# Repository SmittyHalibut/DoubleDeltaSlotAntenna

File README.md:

# Smitty's research into John Portune's Double Delta Skeleton Slot Antenna
This is my directory of stuff.  Let's see, I've got an OpenSCAD model for the top bracket,
I've got some drawings of the switching network I made, I've got the raw NanoVNA data
I collected...  I might have other stuff too, look at README.md files inside the directories.

* Notes and files for my [BayCon 2021](BayCon2021/) presentation
* Raw data, and analysis of data, from [NanoVNA Saver](NanoVNA%20Saver%20Files/) of my build of this antenna.
* Diagram for full [switching network](Switching/)
* OpenSCAD and `.stl` files for my top-of-mast [spreader bracket](Brackets/)

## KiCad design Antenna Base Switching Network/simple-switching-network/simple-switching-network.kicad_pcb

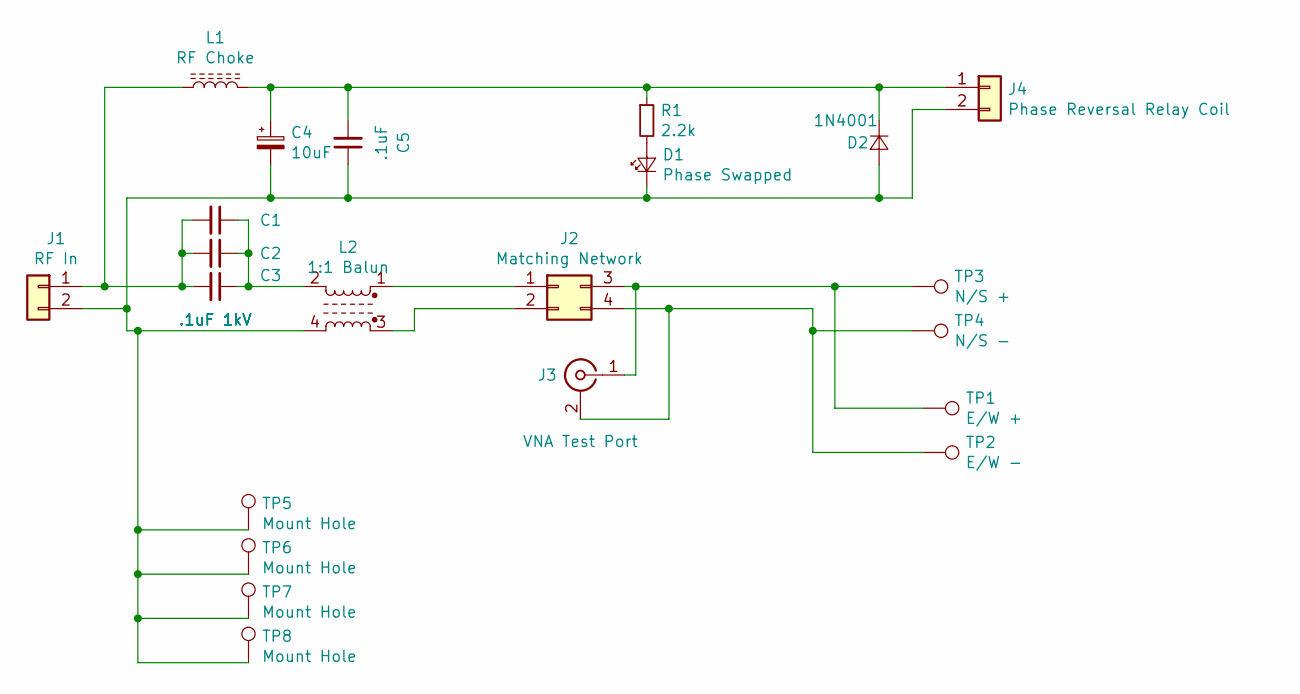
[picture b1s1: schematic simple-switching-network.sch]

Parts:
C1, C2, C3: .1uF 1kV; C_Rect_L10.0mm_W5.0mm_P5.00mm_P7.50mm
C4: 10uF; CP_Radial_D10.0mm_P2.50mm_P5.00mm
C5: .1uF; C_Rect_L7.0mm_W3.5mm_P2.50mm_P5.00mm
D1: Phase Swapped; LED_D5.0mm
D2: 1N4001; D_DO-41_SOD81_P10.16mm_Horizontal
J1: RF In; SolderWirePad_1x02_P5.08mm_Drill1.5mm
J2: Matching Network; MatchingNetworkModule
J3: VNA Test Port; SMA_Amphenol_132134-14_Vertical
J4: Phase Reversal Relay Coil; SolderWirePad_1x02_P5.08mm_Drill1.5mm
L1: RF Choke; L_Toroid_Vertical_L35.6mm_W17.8mm_P12.70mm_Pulse_E
L2: 1:1 Balun; Balun-FT140
R1: 2.2k; R_Axial_DIN0207_L6.3mm_D2.5mm_P10.16mm_Horizontal
TP1: E/W +; MountingHole_3.2mm_M3_Pad
TP2: E/W -; MountingHole_3.2mm_M3_Pad
TP3: N/S +; MountingHole_3.2mm_M3_Pad
TP4: N/S -; MountingHole_3.2mm_M3_Pad
TP5, TP6, TP7, TP8: Mount Hole; MountingHole_3.2mm_M3_Pad

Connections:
unnamed: C1.1, C2.1, C3.1, L2.2
unnamed: C1.2, C2.2, C3.2, J1.1, L1.1
unnamed: C4.1, C5.2, D2.1 (K), J4.1, L1.2, R1.1
unnamed: C4.2, C5.1, D1.1 (K), D2.2 (A), J1.2, J4.2, L2.4, TP5.1, TP6.1, TP7.1, TP8.1
unnamed: D1.2 (A), R1.2
unnamed: J2.1, L2.1
unnamed: J2.2, L2.3
unnamed: J2.3, J3.1 (In), TP1.1, TP3.1
unnamed: J2.4, J3.2 (Ext), TP2.1, TP4.1

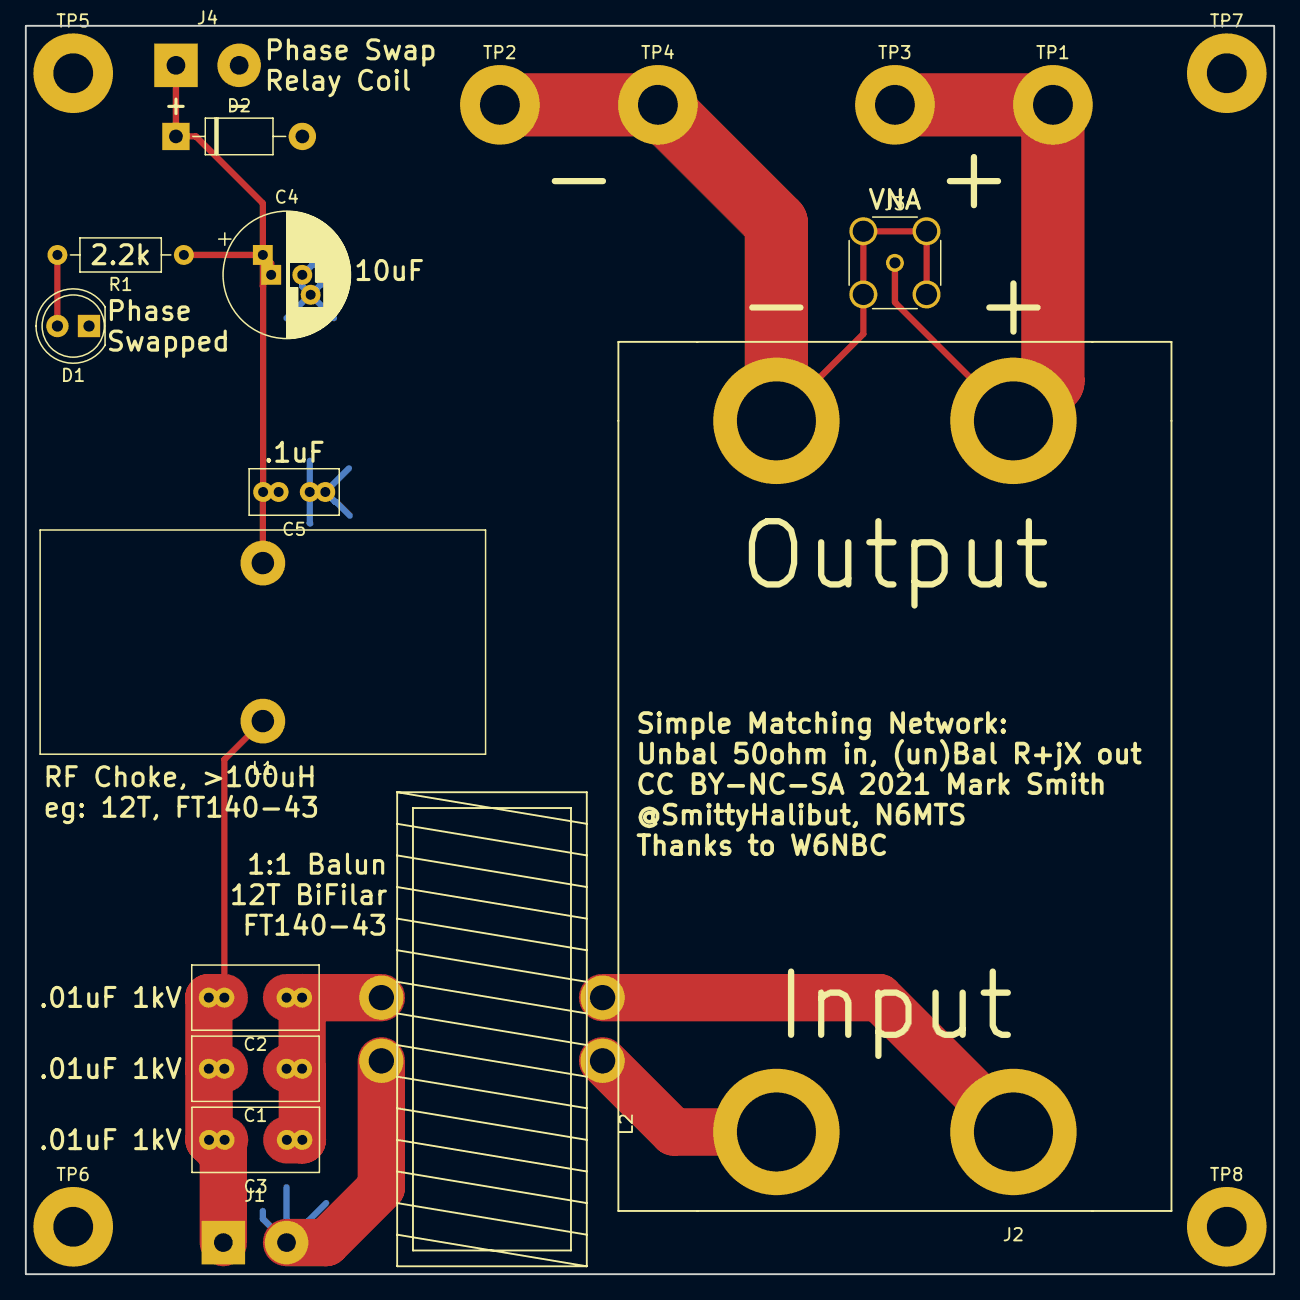
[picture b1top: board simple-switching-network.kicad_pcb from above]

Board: 2 copper layers, 100.3 x 100.3 mm, 22 parts (0 on the bottom side), 9 nets.

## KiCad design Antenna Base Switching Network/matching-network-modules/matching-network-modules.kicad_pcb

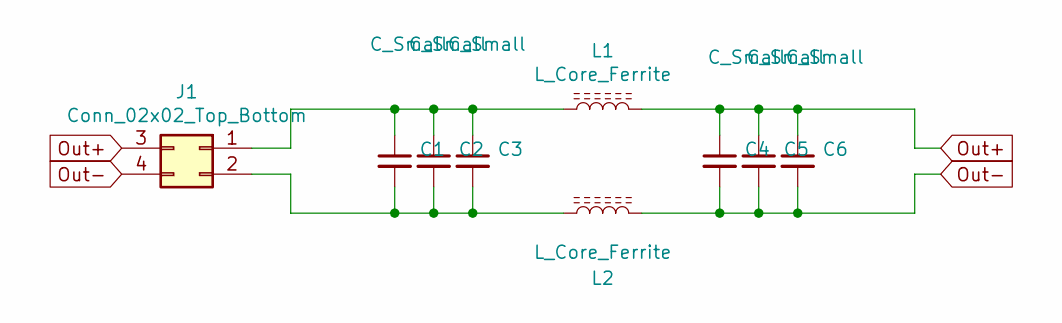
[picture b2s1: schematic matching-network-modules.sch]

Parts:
C1, C4: C_Small; C_Rect_L7.0mm_W3.5mm_P5.00mm
C2, C5: C_Small; C_Rect_L10.0mm_W4.0mm_P7.50mm_FKS3_FKP3
C3, C6: C_Small; C_Rect_L13.0mm_W5.0mm_P10.00mm_FKS3_FKP3_MKS4
J1: Conn_02x02_Top_Bottom; MatchingNetworkModule
L1, L2: L_Core_Ferrite; L_Toroid_Vertical_L41.9mm_W19.1mm_P15.80mm_Vishay_TJ7

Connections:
unnamed: C1.1, C2.1, C3.1, J1.1, L1.1
unnamed: C1.2, C2.2, C3.2, J1.2, L2.1
Out+: C4.1, C5.1, C6.1, J1.3, L1.2
Out-: C4.2, C5.2, C6.2, J1.4, L2.2

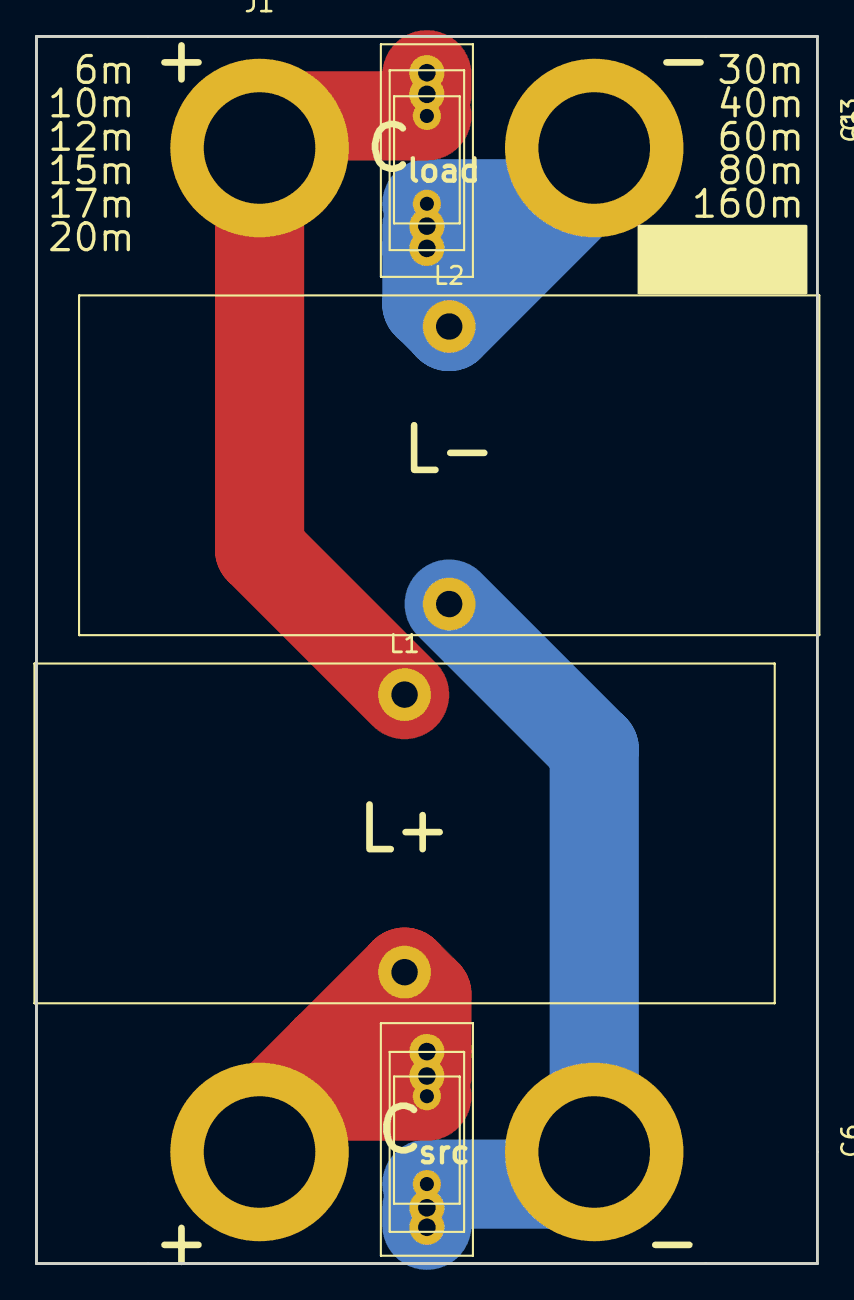
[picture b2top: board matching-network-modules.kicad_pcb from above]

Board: 2 copper layers, 44.4 x 69.8 mm, 9 parts (0 on the bottom side), 4 nets.

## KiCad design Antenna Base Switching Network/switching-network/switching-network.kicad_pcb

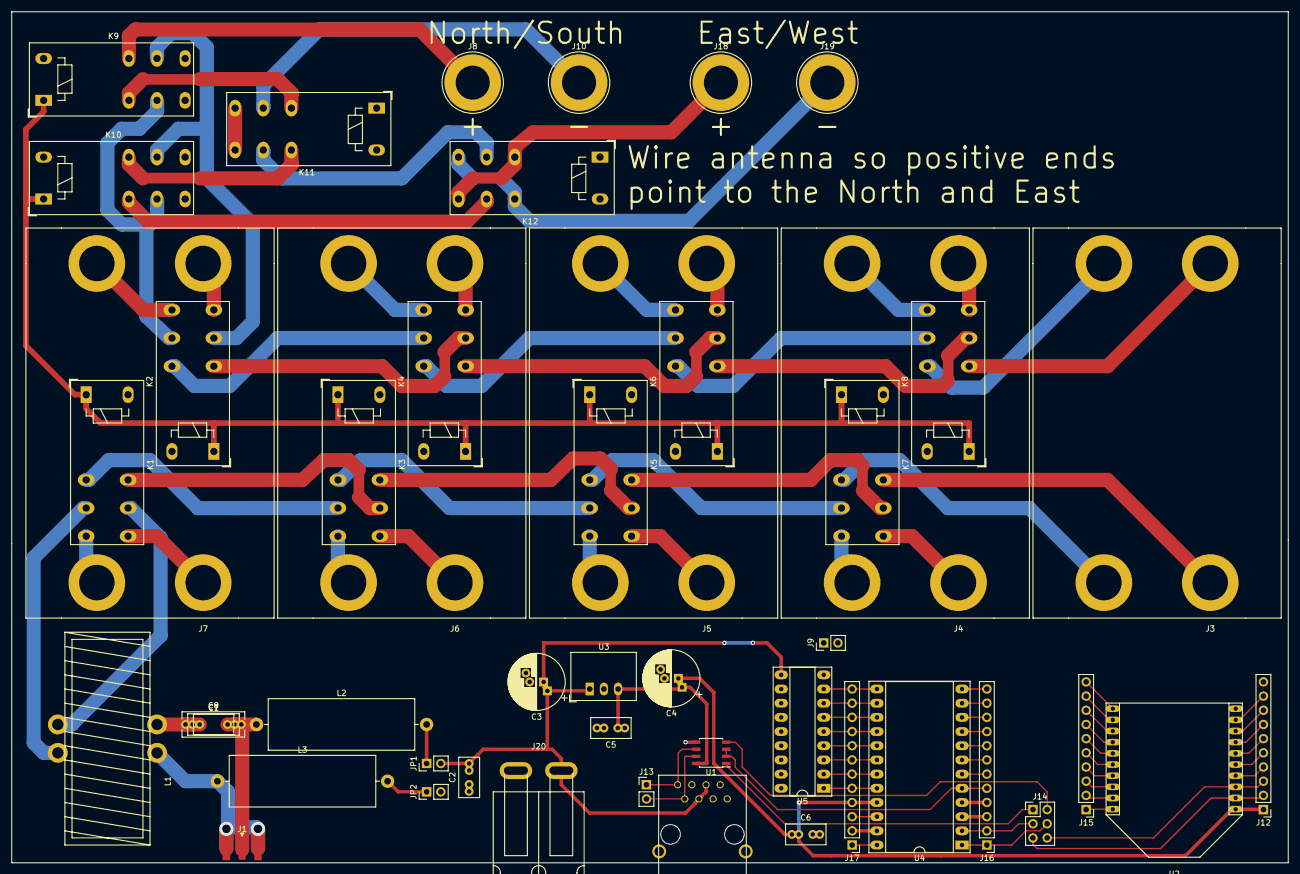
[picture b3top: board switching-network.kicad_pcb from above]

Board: 2 copper layers, 228.6 x 152.4 mm, 49 parts (0 on the bottom side), 103 nets.

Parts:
C1: .1uF; C_Rect_L7.0mm_W3.5mm_P5.00mm
C2, C5, C6: .1uF; C_Rect_L7.0mm_W3.5mm_P2.50mm_P5.00mm
C3, C4: 100uF; CP_Radial_D10.0mm_P2.50mm_P5.00mm
C7: .1uF; C_Rect_L9.0mm_W3.6mm_P7.50mm_MKT
C8: .1uF; C_Rect_L11.0mm_W4.3mm_P10.00mm_MKT
J1: Conn_Coaxial; SMA_Samtec_SMA-J-P-H-ST-EM1_EdgeMount
J3: Module 1 Socket; MatchingNetworkModule
J4: Module 2 Socket; MatchingNetworkModule
J5: Module 3 Socket; MatchingNetworkModule
J6: Module 4 Socket; MatchingNetworkModule
J7: Module 5 Socket; MatchingNetworkModule
J8: NS+; Banana_Jack_1Pin
J9: Simple Bias Tee Rotation Control; PinHeader_1x02_P2.54mm_Vertical
J10: NS-; Banana_Jack_1Pin
J11: 8P8C_Shielded; RJ-45
J12, J15: Test Points; PinHeader_1x10_P2.54mm_Vertical
J13: Test Points; PinHeader_1x02_P2.54mm_Vertical
J14: RS-485 vs XBee; PinHeader_2x03_P2.54mm_Vertical
J16, J17: Test Points; PinHeader_1x12_P2.54mm_Vertical
J18: EW+; Banana_Jack_1Pin
J19: EW-; Banana_Jack_1Pin
J20: +12v Power; AndersonPP45
JP1, JP2: Jumper_NC_Small; PinHeader_1x02_P2.54mm_Vertical
K1, K2, K3, K4, K5, K6, K7, K8: RT42xxxx; Relay_DPDT_Schrack-RT2-FormC_RM5mm
K9: N/S Disable; Relay_DPDT_Schrack-RT2-FormC_RM5mm
K10: E/W Disable; Relay_DPDT_Schrack-RT2-FormC_RM5mm
K11: Series Enable; Relay_DPDT_Schrack-RT2-FormC_RM5mm
K12: E/W Reverse; Relay_DPDT_Schrack-RT2-FormC_RM5mm
L1: 1:1 Balun; Balun-FT140
L2, L3: RF Choke; L_Axial_L26.0mm_D9.0mm_P30.48mm_Horizontal_Fastron_77A
U1: SN65HVD10-EP; SOIC-8_3.9x4.9mm_P1.27mm
U2: XBeeModule
U3: R-783.3-0.5; Converter_DCDC_RECOM_R-78E-0.5_THT
U4: Leonardo_Pro_Micro; DIP-24_W15.24mm_Socket_LongPads
U5: ULN2803A; DIP-18_W7.62mm_Socket_LongPads

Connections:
+3V3: C4.1, C5.1, C6.1, J12.1, J17.4, U1.8, U2.1, U3.3, U4.21
+12V: C2.2, C3.1, J11.4, J11.5, J20.1, JP1.2, K1.A1, K2.A1, K3.A1, K4.A1, K5.A1, K6.A1, K7.A1, K8.A1, K9.A1, K10.A1, K11.A1, K12.A1, U3.1, U5.10
EWDisable: K10.A2, U5.12
EWReverse: J9.1, K12.A2, U5.16
GND: C2.1, C3.2, C4.2, C5.2, C6.2, J9.2, J11.7, J11.8, J12.10, J16.3, J16.4, J17.2, J20.2, JP2.2, U1.5, U2.10, U3.2, U4.3, U4.4, U4.23, U5.9
MatchedRFOut+: K2.11, K9.21, K10.21
MatchedRFOut-: K2.21, K9.11, K10.11
Mod2En: K7.A2, K8.A2, U5.18
Mod3En: K5.A2, K6.A2, U5.17
Mod4En: K3.A2, K4.A2, U5.14
Mod5En: K1.A2, K2.A2, U5.13
ModIn1+: J3.1, K7.22
ModIn1-: J3.2, K7.12
ModIn2+: J4.1, K7.24
ModIn2-: J4.2, K7.14
ModIn3+: J5.1, K5.24
ModIn3-: J5.2, K5.14
ModIn4+: J6.1, K3.24
ModIn4-: J6.2, K3.14
ModIn5+: J7.1, K1.24
ModIn5-: J7.2, K1.14
ModOut1+: J3.3, K8.12
ModOut1-: J3.4, K8.22
ModOut2+: J4.3, K8.14
ModOut2-: J4.4, K8.24
ModOut3+: J5.3, K6.14
ModOut3-: J5.4, K6.24
ModOut4+: J6.3, K4.14
ModOut4-: J6.4, K4.24
ModOut5+: J7.3, K2.14
ModOut5-: J7.4, K2.24
NSDisable: K9.A2, U5.11
unnamed: C1.1, C7.1, C8.1, L1.1
unnamed: C1.2, C7.2, C8.2, J1.1, L2.1
unnamed: J1.2, L1.3, L3.1
unnamed: J8.1, K9.22
unnamed: J10.1, K11.11
unnamed: J11.1, J13.1, U1.6
unnamed: J11.2, J13.2, U1.7
unnamed: J12.4, U2.4
unnamed: J12.5, U2.5
unnamed: J12.6, U2.6
unnamed: J12.7, U2.7
unnamed: J12.8, U2.8
unnamed: J12.9, U2.9
unnamed: J15.1, U2.20
unnamed: J15.2, U2.19
unnamed: J15.3, U2.18
unnamed: J15.4, U2.17
unnamed: J15.5, U2.16
unnamed: J15.6, U2.15
unnamed: J15.7, U2.14
unnamed: J15.8, U2.13
unnamed: J15.9, U2.12
unnamed: J15.10, U2.11
unnamed: J16.6, U4.6
unnamed: J16.7, U4.7
unnamed: J16.8, U4.8
unnamed: J16.9, U4.9
unnamed: J16.10, U4.10
unnamed: J16.11, U4.11
unnamed: J16.12, U4.12
unnamed: J17.1, U4.24
unnamed: J17.5, U4.20, U5.1
unnamed: J17.6, U4.19, U5.2
unnamed: J17.7, U4.18, U5.3
unnamed: J17.8, U4.17, U5.4
unnamed: J17.9, U4.16, U5.5
unnamed: J17.10, U4.15, U5.6
unnamed: J17.11, U4.14, U5.7
unnamed: J17.12, U4.13, U5.8
unnamed: J18.1, K12.12, K12.24
unnamed: J19.1, K12.14, K12.22
unnamed: JP1.1, L2.2
unnamed: JP2.1, L3.2
unnamed: K1.11, L1.4
unnamed: K1.12, K3.11
unnamed: K1.21, L1.2
unnamed: K1.22, K3.21
unnamed: K2.12, K4.11
unnamed: K2.22, K4.21
unnamed: K3.12, K5.11
unnamed: K3.22, K5.21
unnamed: K4.12, K6.11
unnamed: K4.22, K6.21
unnamed: K5.12, K7.11
unnamed: K5.22, K7.21
unnamed: K6.12, K8.11
unnamed: K6.22, K8.21
unnamed: K10.12, K12.21
unnamed: K10.22, K11.22
unnamed: K9.12, K11.12
unnamed: K11.14, K11.24
unnamed: K11.21, K12.11
Reset: J17.3, U4.22
Rx485: J14.2, U1.4
RxMicro: J14.3, J16.2, U4.2
RxXBee: J12.3, J14.6, U2.3
SeriesEnable: K11.A2, U5.15
Tx485: J14.1, U1.1
TxEn485: J16.5, U1.2, U1.3, U4.5
TxMicro: J14.4, J16.1, U4.1
TxXBee: J12.2, J14.5, U2.2

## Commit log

2020-10-18 Initial commit: OpenSCAD bracket for mast topper, NanoVNA raw data files, and drawings of the switching network I made for researching.
2020-10-18 Images of the NanoVNA-Saver screen showing the stats for 40m, 30m, 20m, 15m, and 10m
2020-10-18 Adding detail to the README
2020-10-18 Adding link to nanovna-saver
2020-12-29 Analyzing S parameters into matching networks.
2020-12-29 Link to local file?
2020-12-29 Making a note box
2020-12-29 Damn note boxes
2020-12-29 Fixing bullet lists.
2021-01-02 Moved s1p files to dated directories. Added Actual matching network and actual impedance calculations to `make_matching_network.py`.
2021-01-06 Removed old .s1p files that were not properly calibrated; they can't be trusted at all. (They're still in git history if you really want them.) Added files from 2021-01-05 that were taken after prope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
2021-01-06 Spelling
2021-01-06 Added link to 2021-01-05 Twitter thread.
2021-01-06 Added on-air observations from the shack, and reorganized a bit.
2021-01-06 Fixed feedline length for the H422
2021-01-09 Rearranged the code in `make_matching_network.py` to make it easier to work on. Added a column showing the Actual Impedance if you made a single matching network for the given band.
2021-01-16 Reorganized the output of `make_matching_network.py` to group by band instead of file, and made output Markdown. Output of 2021-01-05 data in [2021-01-05/README.md](2021-01-05/README.md)
2021-01-18 Added my analysis of 2021-01-5 data to README.md
2021-01-23 Outline for my BayCon2021 talk.
2021-01-24 First draft of BayCon 2021 presentation.
2021-01-24 Updates to the BayCon slides
2021-05-08 A simple balanced matching network module, and remote control board with balun and bias tee power for phase reversal relay. As ordered: 2021-05-08
2021-05-08 A more feature-full (read: complex) base-of-antenna switching network: Switches multiple matching networks, will switch different antenna configurations, etc. THIS IS NOT COMPLETE.
2021-05-09 .gitignore, so it doesn't keep trying to add videos to git.

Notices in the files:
Antenna Base Switching Network/simple-switching-network/simple-switching-network.kicad_pcb:
CC BY-NC-SA 2021 Mark Smith
